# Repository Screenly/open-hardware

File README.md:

# open-hardware
Repository for Screenly's open hardware projects.

## License

Copyright Screenly, Inc.

This source describes Open Hardware and is licensed under the CERN-OHL-P v2 (SPDX: `CERN-OHL-P-2.0`). See [LICENSE](LICENSE) for the full text.

You may redistribute and modify this source and make products using it under the terms of the CERN-OHL-P v2 (https://cern.ch/cern-ohl).

This source is distributed WITHOUT ANY EXPRESS OR IMPLIED WARRANTY, INCLUDING OF MERCHANTABILITY, SATISFACTORY QUALITY AND FITNESS FOR A PARTICULAR PURPOSE. Please see the CERN-OHL-P v2 for applicable conditions.

Source location: https://github.com/Screenly/open-hardware

Third-party 3D models in `library/3d-models` come from component manufacturers and the KiCad libraries, and remain under their owners' terms.

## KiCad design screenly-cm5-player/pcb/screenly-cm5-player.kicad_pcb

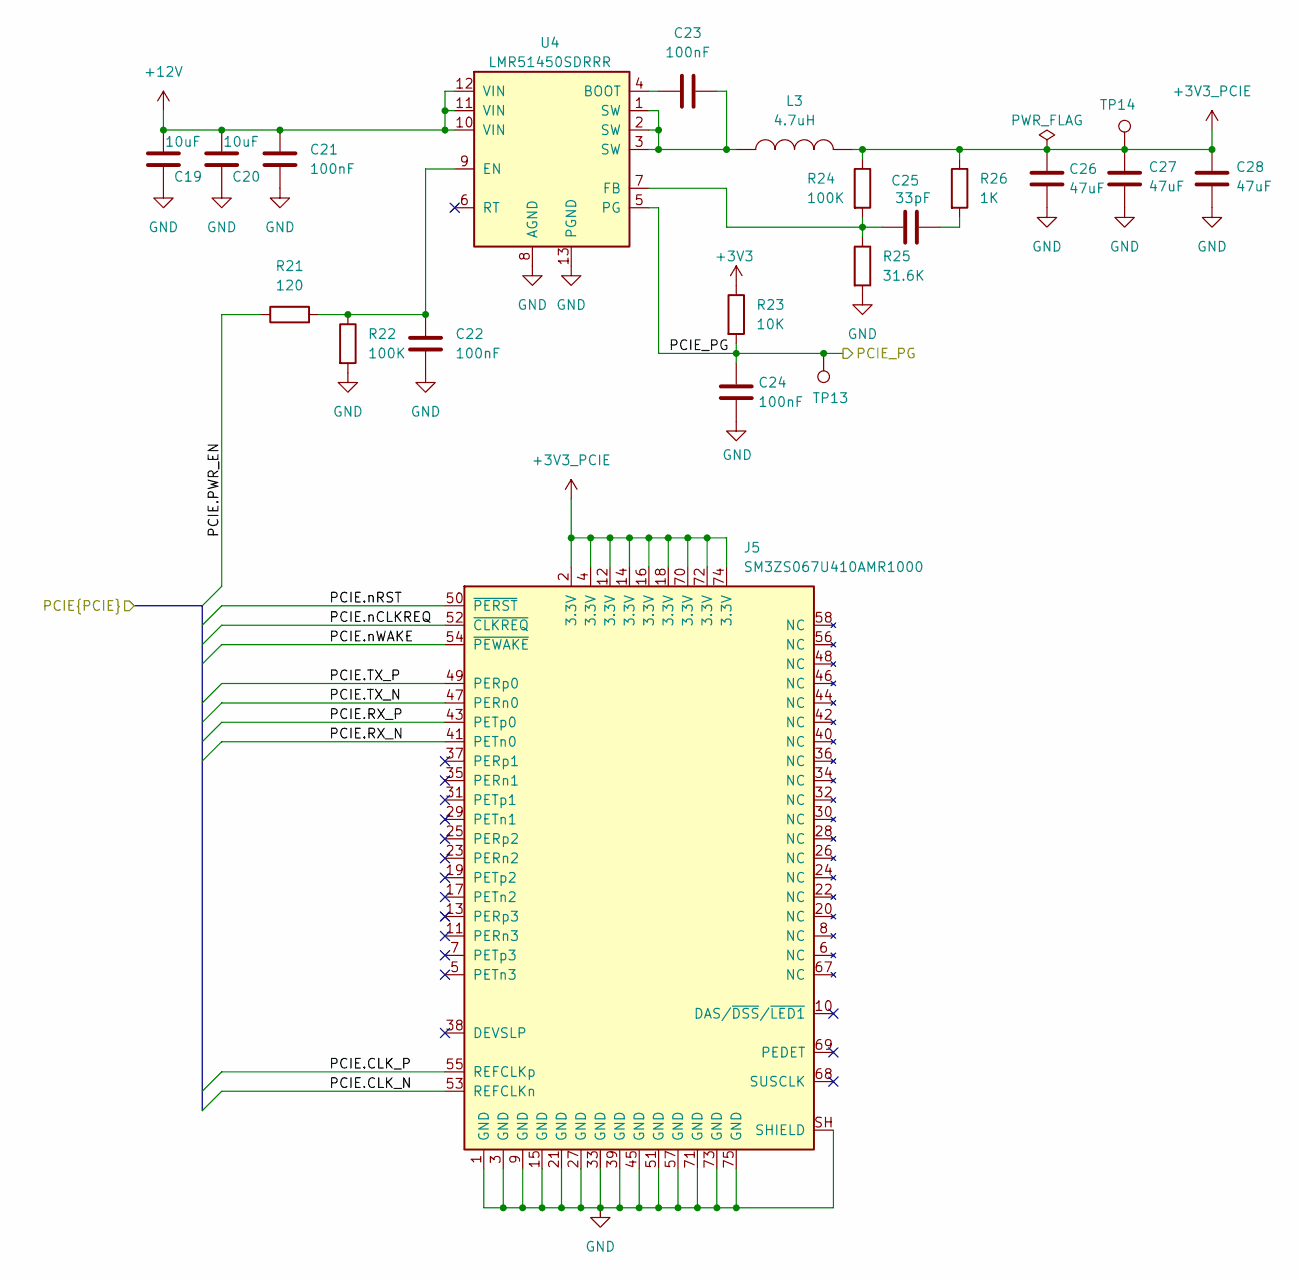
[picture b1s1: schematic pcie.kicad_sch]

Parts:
C19, C20: 10uF; C_1210; tolerance 10%; voltage 50V; PartNumber SRLY-CAP-000002
C21, C22, C23, C24: 100nF; C_0402; tolerance 10%; voltage 50V; PartNumber SRLY-CAP-000001
C25: 33pF; C_0402; tolerance 5%; voltage 50V; PartNumber SRLY-CAP-000003
C26, C27, C28: 47uF; C_1210; tolerance 10%; voltage 10V; PartNumber SRLY-CAP-000005
J5: SM3ZS067U410AMR1000; M2_M-Key_JAE_SM3ZS067U410AMR1000_2230_2242_2280; PartNumber SRLY-CON-000006
L3: 4.7uH; L_Coilank_AAPS1050; tolerance 20%; PartNumber SRLY-IND-000001
R21: 120; R_0402; tolerance 5%; voltage 50V; PartNumber SRLY-RES-000009
R22, R24: 100K; R_0402; tolerance 1%; voltage 50V; PartNumber SRLY-RES-000004
R23: 10K; R_0402; tolerance 1%; voltage 50V; PartNumber SRLY-RES-000005
R25: 31.6K; R_0402; tolerance 1%; voltage 50V; PartNumber SRLY-RES-000010
R26: 1K; R_0402; tolerance 5%; voltage 50V; PartNumber SRLY-RES-000006
TP13, TP14: TestPoint; TestPoint_Pad_D2.0mm
U4: LMR51450SDRRR; TI_WSON-12-1EP_3x3mm_P0.5mm_EP1.3x2.5mm; PartNumber SRLY-PWR-000001

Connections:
+3V3: R23.1; also elsewhere on the board
+3V3_PCIE: C26.1, C27.1, C28.1, J5.2 (3.3V), J5.4 (3.3V), J5.12 (3.3V), J5.14 (3.3V), J5.16 (3.3V), J5.18 (3.3V), J5.70 (3.3V), J5.72 (3.3V), J5.74 (3.3V), L3.2, R24.1, R26.1, TP14.1 (1_1)
+12V: C19.1, C20.1, C21.1, U4.10 (VIN), U4.11 (VIN), U4.12 (VIN); also elsewhere on the board
/Compute Module/PCIE.CLK_N: J5.53 (REFCLKn); also elsewhere on the board
/Compute Module/PCIE.CLK_P: J5.55 (REFCLKp); also elsewhere on the board
/Compute Module/PCIE.PWR_EN: R21.1; also elsewhere on the board
/Compute Module/PCIE.RX_N: J5.41 (PETn0); also elsewhere on the board
/Compute Module/PCIE.RX_P: J5.43 (PETp0); also elsewhere on the board
/Compute Module/PCIE.TX_N: J5.47 (PERn0); also elsewhere on the board
/Compute Module/PCIE.TX_P: J5.49 (PERp0); also elsewhere on the board
/Compute Module/PCIE.nCLKREQ: J5.52 (~CLKREQ); also elsewhere on the board
/Compute Module/PCIE.nRST: J5.50 (~PERST); also elsewhere on the board
/Compute Module/PCIE.nWAKE: J5.54 (~PEWAKE); also elsewhere on the board
/PCIE_PG: C24.2, R23.2, TP13.1 (1_1), U4.5 (PG); also elsewhere on the board
GND: C19.2, C20.2, C21.2, C22.1, C24.1, C26.2, C27.2, C28.2, J5.1 (GND), J5.3 (GND), J5.9 (GND), J5.15 (GND), J5.21 (GND), J5.27 (GND), J5.33 (GND), J5.39 (GND), J5.45 (GND), J5.51 (GND), J5.57 (GND), J5.71 (GND), J5.73 (GND), J5.75 (GND), J5.SH (SHIELD), R22.2, R25.2, U4.8 (AGND), U4.13 (PGND); also elsewhere on the board
unnamed: C23.2, L3.1, U4.1 (SW), U4.2 (SW), U4.3 (SW)
unnamed: C25.2, R26.2
unnamed: C23.1, U4.4 (BOOT)
unnamed: C22.2, R21.2, R22.1, U4.9 (EN)
unnamed: C25.1, R24.2, R25.1, U4.7 (FB)

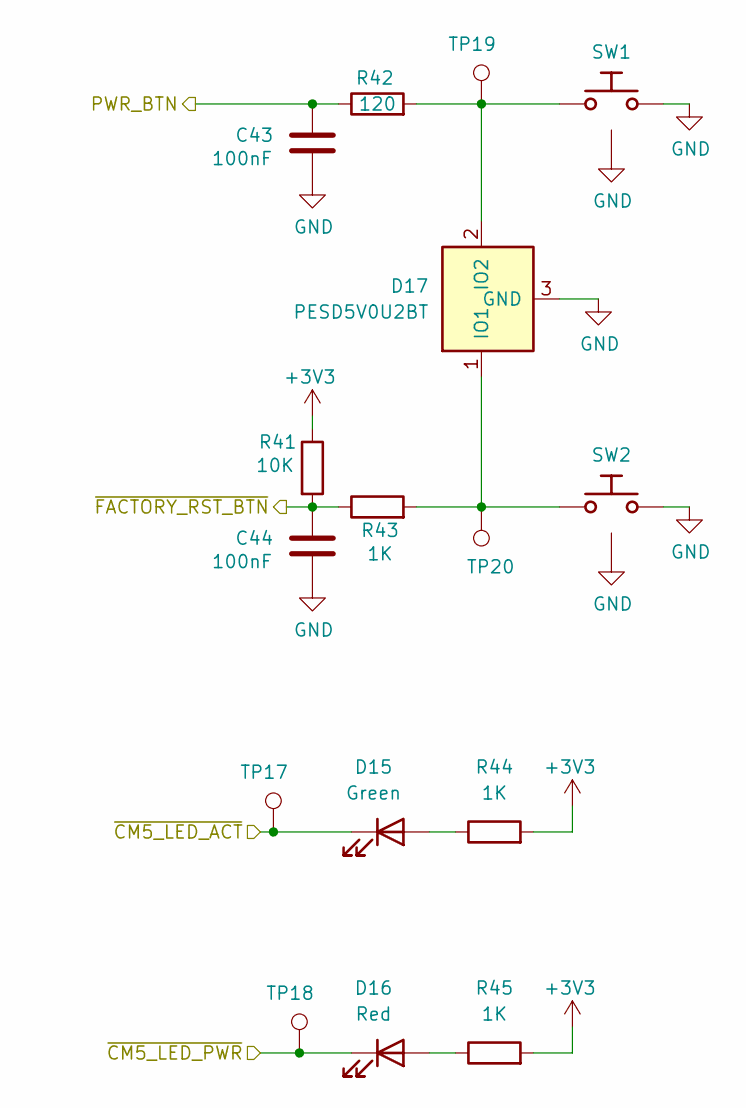
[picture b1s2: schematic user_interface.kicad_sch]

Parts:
C43, C44: 100nF; C_0402; tolerance 10%; voltage 50V; PartNumber SRLY-CAP-000001
D15: Green; LED_LiteOn_LTST-S270_SideView; PartNumber SRLY-LED-000002
D16: Red; LED_LiteOn_LTST-S270_SideView; PartNumber SRLY-LED-000001
D17: PESD5V0U2BT; SOT-23; PartNumber SRLY-DIO-000005
R41: 10K; R_0402; tolerance 1%; voltage 50V; PartNumber SRLY-RES-000005
R42: 120; R_0402; tolerance 5%; voltage 50V; PartNumber SRLY-RES-000009
R43, R44, R45: 1K; R_0402; tolerance 5%; voltage 50V; PartNumber SRLY-RES-000006
SW1, SW2: PTS645VM31-2; SW_Tactile_SPST_Angled_PTS645Vx58-2LFS; voltage 12V; PartNumber SRLY-SWC-000002
TP17, TP18, TP19, TP20: TestPoint; TestPoint_Pad_D2.0mm

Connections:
+3V3: R41.1, R44.2, R45.2; also elsewhere on the board
/Compute Module/PWR_BTN: C43.1, R42.1; also elsewhere on the board
/Compute Module/~CM5_LED_ACT: D15.1 (K), TP17.1 (1_1); also elsewhere on the board
/Compute Module/~CM5_LED_PWR: D16.1 (K), TP18.1 (1_1); also elsewhere on the board
/Compute Module/~FACTORY_RST_BTN: C44.1, R41.2, R43.1; also elsewhere on the board
GND: C43.2, C44.2, D17.3 (GND), SW1.2, SW1.SH, SW2.2, SW2.SH; also elsewhere on the board
unnamed: D15.2 (A), R44.1
unnamed: D16.2 (A), R45.1
unnamed: D17.1 (IO1), R43.2, SW2.1, TP20.1 (1_1)
unnamed: D17.2 (IO2), R42.2, SW1.1, TP19.1 (1_1)

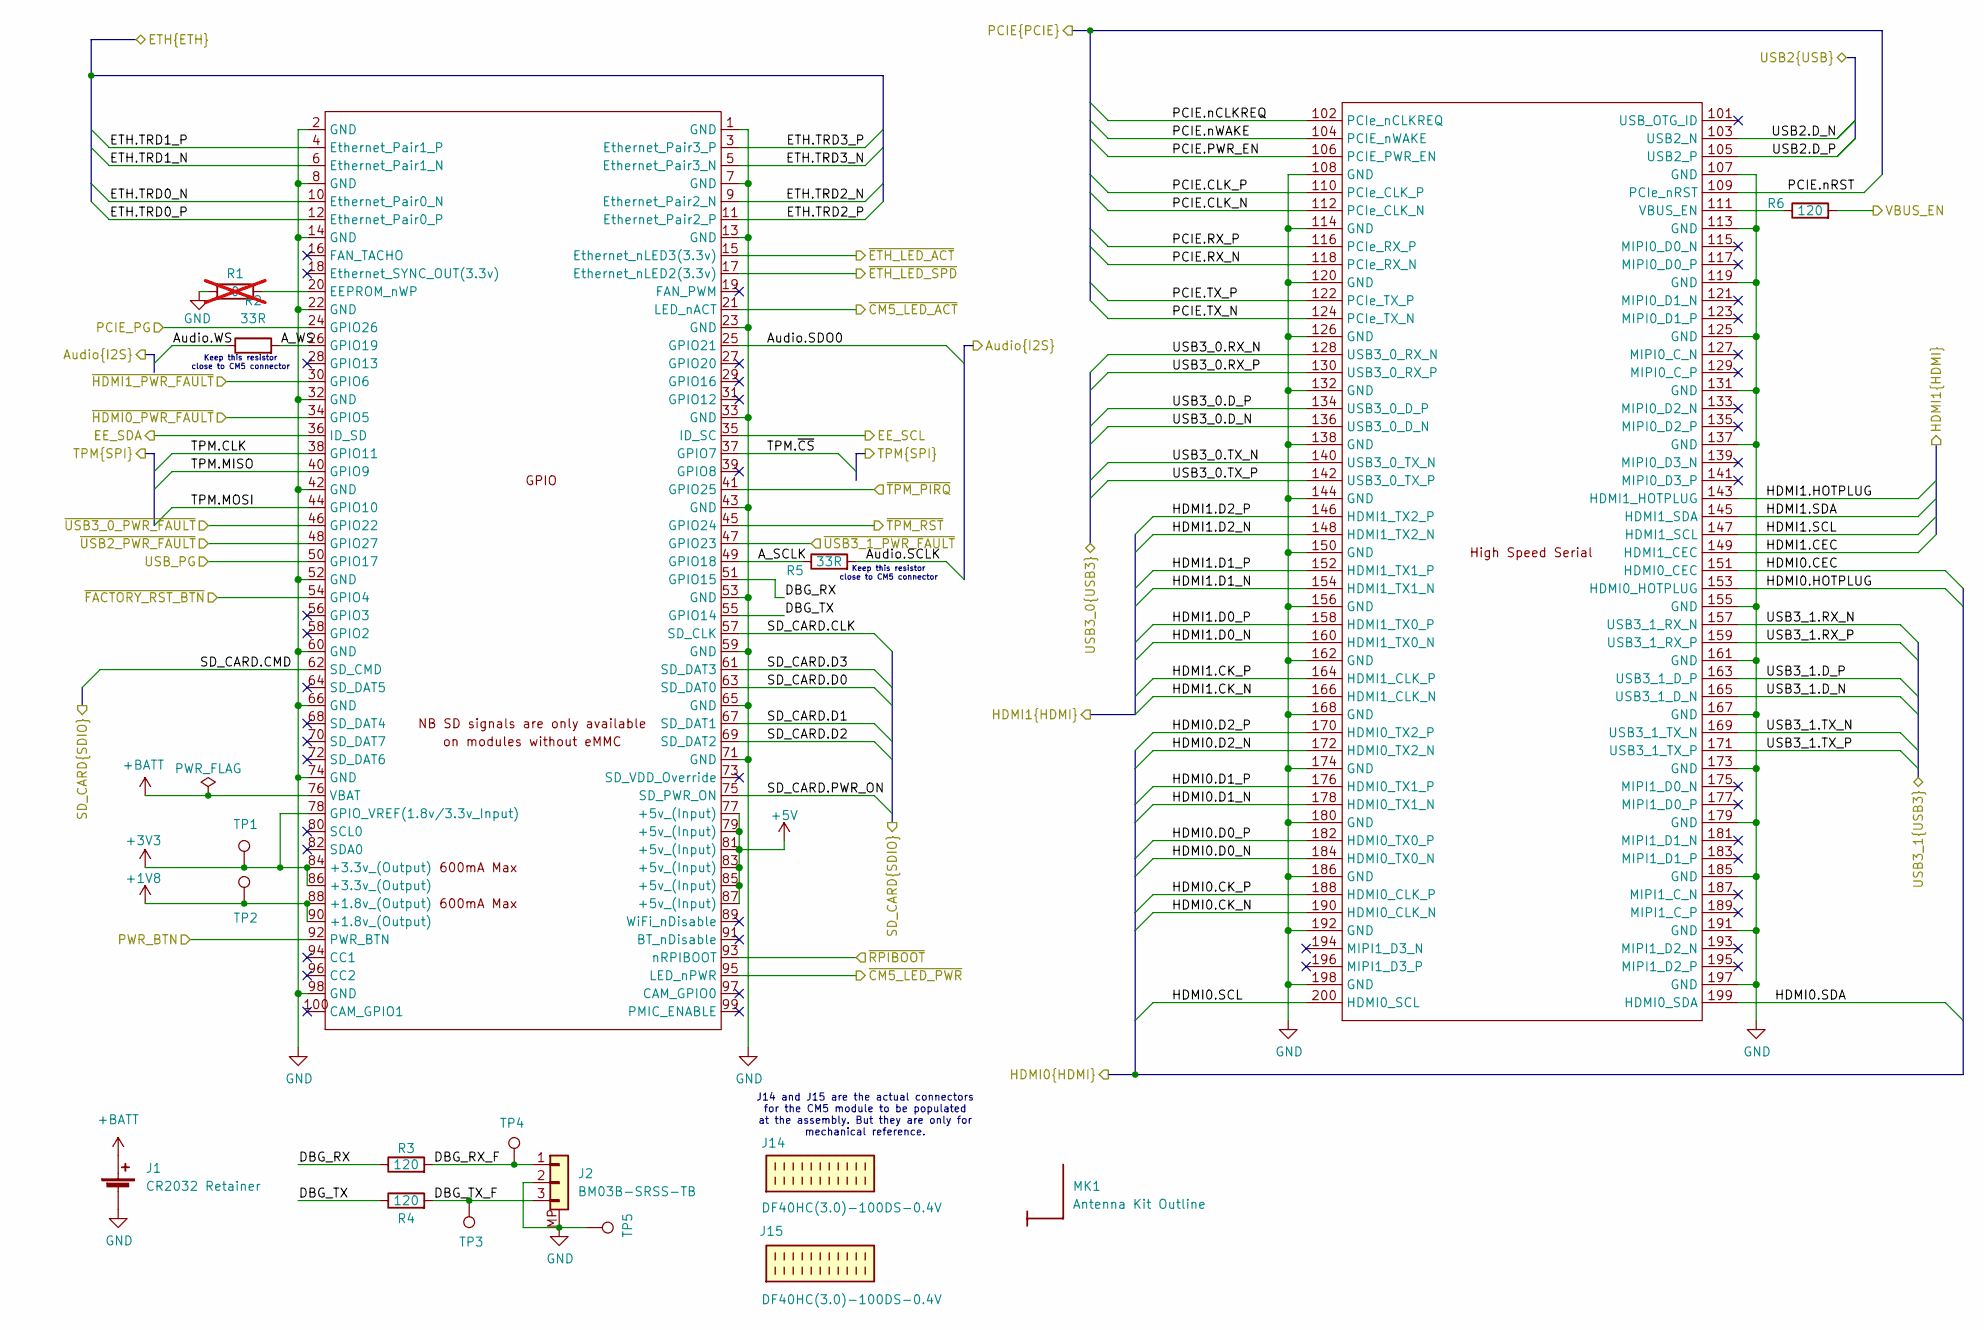
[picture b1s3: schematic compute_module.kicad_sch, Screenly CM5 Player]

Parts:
J1: CR2032 Retainer; BatteryHolder_MYOUNG_MY-2032-08_CR2032; PartNumber SRLY-CON-000014
J2: BM03B-SRSS-TB; JST_SH_BM03B-SRSS-TB_1x03-1MP_P1.00mm_Vertical; voltage 50V; PartNumber SRLY-CON-000015
J14, J15: DF40HC(3.0)-100DS-0.4V; Hirose_DF40HC-3.0-100DS-0.4V_2x50_P0.4mm_Vertical_NoCopper; PartNumber SRLY-CON-000016
MK1: Antenna Kit Outline; RaspberryPi_Antenna_Kit_Outline_SideView
R1: 0; SolderBridge_0402; tolerance 1%; voltage 50V; PartNumber SRLY-RES-000008; not fitted
R2, R5: 33R; R_0402; tolerance 5%; voltage 50V; PartNumber SRLY-RES-000014
R3, R4, R6: 120; R_0402; tolerance 5%; voltage 50V; PartNumber SRLY-RES-000009
TP1, TP2, TP3, TP4, TP5: TestPoint; TestPoint_Pad_D2.0mm
U1: CM5104064; RaspberryPi-CM5; PartNumber SRLY-MOD-000001

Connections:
+1V8: TP2.1 (1_1), U1.88 (+1.8v_(Output)), U1.90 (+1.8v_(Output))
+3V3: TP1.1 (1_1), U1.78 (GPIO_VREF(1.8v/3.3v_Input)), U1.84 (+3.3v_(Output)), U1.86 (+3.3v_(Output)); also elsewhere on the board
+5V: U1.77 (+5v_(Input)), U1.79 (+5v_(Input)), U1.81 (+5v_(Input)), U1.83 (+5v_(Input)), U1.85 (+5v_(Input)), U1.87 (+5v_(Input)); also elsewhere on the board
+BATT: J1.1 (+), U1.76 (VBAT)
/Analog Audio/Audio.SCLK: R5.2; also elsewhere on the board
/Analog Audio/Audio.SDO0: U1.25 (GPIO21); also elsewhere on the board
/Analog Audio/Audio.WS: R2.1; also elsewhere on the board
/Compute Module/A_SCLK: R5.1, U1.49 (GPIO18)
/Compute Module/A_WS: R2.2, U1.26 (GPIO19)
/Compute Module/DBG_RX: R3.1, U1.51 (GPIO15)
/Compute Module/DBG_RX_F: J2.1, R3.2, TP4.1 (1_1)
/Compute Module/DBG_TX: R4.1, U1.55 (GPIO14)
/Compute Module/DBG_TX_F: J2.3, R4.2, TP3.1 (1_1)
/Compute Module/EE_SCL: U1.35 (ID_SC); also elsewhere on the board
/Compute Module/EE_SDA: U1.36 (ID_SD); also elsewhere on the board
/Compute Module/ETH.TRD0_N: U1.10 (Ethernet_Pair0_N); also elsewhere on the board
/Compute Module/ETH.TRD0_P: U1.12 (Ethernet_Pair0_P); also elsewhere on the board
/Compute Module/ETH.TRD1_N: U1.6 (Ethernet_Pair1_N); also elsewhere on the board
/Compute Module/ETH.TRD1_P: U1.4 (Ethernet_Pair1_P); also elsewhere on the board
/Compute Module/ETH.TRD2_N: U1.9 (Ethernet_Pair2_N); also elsewhere on the board
/Compute Module/ETH.TRD2_P: U1.11 (Ethernet_Pair2_P); also elsewhere on the board
/Compute Module/ETH.TRD3_N: U1.5 (Ethernet_Pair3_N); also elsewhere on the board
/Compute Module/ETH.TRD3_P: U1.3 (Ethernet_Pair3_P); also elsewhere on the board
/Compute Module/HDMI0.CEC: U1.151 (HDMI0_CEC); also elsewhere on the board
/Compute Module/HDMI0.CK_N: U1.190 (HDMI0_CLK_N); also elsewhere on the board
/Compute Module/HDMI0.CK_P: U1.188 (HDMI0_CLK_P); also elsewhere on the board
/Compute Module/HDMI0.D0_N: U1.184 (HDMI0_TX0_N); also elsewhere on the board
/Compute Module/HDMI0.D0_P: U1.182 (HDMI0_TX0_P); also elsewhere on the board
/Compute Module/HDMI0.D1_N: U1.178 (HDMI0_TX1_N); also elsewhere on the board
/Compute Module/HDMI0.D1_P: U1.176 (HDMI0_TX1_P); also elsewhere on the board
/Compute Module/HDMI0.D2_N: U1.172 (HDMI0_TX2_N); also elsewhere on the board
/Compute Module/HDMI0.D2_P: U1.170 (HDMI0_TX2_P); also elsewhere on the board
/Compute Module/HDMI0.HOTPLUG: U1.153 (HDMI0_HOTPLUG); also elsewhere on the board
/Compute Module/HDMI0.SCL: U1.200 (HDMI0_SCL); also elsewhere on the board
/Compute Module/HDMI0.SDA: U1.199 (HDMI0_SDA); also elsewhere on the board
/Compute Module/HDMI1.CEC: U1.149 (HDMI1_CEC); also elsewhere on the board
/Compute Module/HDMI1.CK_N: U1.166 (HDMI1_CLK_N); also elsewhere on the board
/Compute Module/HDMI1.CK_P: U1.164 (HDMI1_CLK_P); also elsewhere on the board
/Compute Module/HDMI1.D0_N: U1.160 (HDMI1_TX0_N); also elsewhere on the board
/Compute Module/HDMI1.D0_P: U1.158 (HDMI1_TX0_P); also elsewhere on the board
/Compute Module/HDMI1.D1_N: U1.154 (HDMI1_TX1_N); also elsewhere on the board
/Compute Module/HDMI1.D1_P: U1.152 (HDMI1_TX1_P); also elsewhere on the board
/Compute Module/HDMI1.D2_N: U1.148 (HDMI1_TX2_N); also elsewhere on the board
/Compute Module/HDMI1.D2_P: U1.146 (HDMI1_TX2_P); also elsewhere on the board
/Compute Module/HDMI1.HOTPLUG: U1.143 (HDMI1_HOTPLUG); also elsewhere on the board
/Compute Module/HDMI1.SCL: U1.147 (HDMI1_SCL); also elsewhere on the board
/Compute Module/HDMI1.SDA: U1.145 (HDMI1_SDA); also elsewhere on the board
/Compute Module/PCIE.CLK_N: U1.112 (PCIe_CLK_N); also elsewhere on the board
/Compute Module/PCIE.CLK_P: U1.110 (PCIe_CLK_P); also elsewhere on the board
/Compute Module/PCIE.PWR_EN: U1.106 (PCIE_PWR_EN); also elsewhere on the board
/Compute Module/PCIE.RX_N: U1.118 (PCIe_RX_N); also elsewhere on the board
/Compute Module/PCIE.RX_P: U1.116 (PCIe_RX_P); also elsewhere on the board
/Compute Module/PCIE.TX_N: U1.124 (PCIe_TX_N); also elsewhere on the board
/Compute Module/PCIE.TX_P: U1.122 (PCIe_TX_P); also elsewhere on the board
/Compute Module/PCIE.nCLKREQ: U1.102 (PCIe_nCLKREQ); also elsewhere on the board
/Compute Module/PCIE.nRST: U1.109 (PCIe_nRST); also elsewhere on the board
/Compute Module/PCIE.nWAKE: U1.104 (PCIE_nWAKE); also elsewhere on the board
/Compute Module/PWR_BTN: U1.92 (PWR_BTN); also elsewhere on the board
/Compute Module/SD_CARD.CLK: U1.57 (SD_CLK); also elsewhere on the board
/Compute Module/SD_CARD.CMD: U1.62 (SD_CMD); also elsewhere on the board
/Compute Module/SD_CARD.D0: U1.63 (SD_DAT0); also elsewhere on the board
/Compute Module/SD_CARD.D1: U1.67 (SD_DAT1); also elsewhere on the board
/Compute Module/SD_CARD.D2: U1.69 (SD_DAT2); also elsewhere on the board
/Compute Module/SD_CARD.D3: U1.61 (SD_DAT3); also elsewhere on the board
/Compute Module/SD_CARD.PWR_ON: U1.75 (SD_PWR_ON); also elsewhere on the board
/Compute Module/TPM.CLK: U1.38 (GPIO11); also elsewhere on the board
/Compute Module/TPM.MISO: U1.40 (GPIO9); also elsewhere on the board
/Compute Module/TPM.MOSI: U1.44 (GPIO10); also elsewhere on the board
/Compute Module/TPM.~CS: U1.37 (GPIO7); also elsewhere on the board
/Compute Module/USB2.D_N: U1.103 (USB2_N); also elsewhere on the board
/Compute Module/USB2.D_P: U1.105 (USB2_P); also elsewhere on the board
/Compute Module/USB3_0.D_N: U1.136 (USB3_0_D_N); also elsewhere on the board
/Compute Module/USB3_0.D_P: U1.134 (USB3_0_D_P); also elsewhere on the board
/Compute Module/USB3_0.RX_N: U1.128 (USB3_0_RX_N); also elsewhere on the board
/Compute Module/USB3_0.RX_P: U1.130 (USB3_0_RX_P); also elsewhere on the board
/Compute Module/USB3_0.TX_N: U1.140 (USB3_0_TX_N); also elsewhere on the board
/Compute Module/USB3_0.TX_P: U1.142 (USB3_0_TX_P); also elsewhere on the board
/Compute Module/USB3_1.D_N: U1.165 (USB3_1_D_N); also elsewhere on the board
/Compute Module/USB3_1.D_P: U1.163 (USB3_1_D_P); also elsewhere on the board
/Compute Module/USB3_1.RX_N: U1.157 (USB3_1_RX_N); also elsewhere on the board
/Compute Module/USB3_1.RX_P: U1.159 (USB3_1_RX_P); also elsewhere on the board
/Compute Module/USB3_1.TX_N: U1.169 (USB3_1_TX_N); also elsewhere on the board
/Compute Module/USB3_1.TX_P: U1.171 (USB3_1_TX_P); also elsewhere on the board
/Compute Module/VBUS_EN: R6.2; also elsewhere on the board
/Compute Module/~CM5_LED_ACT: U1.21 (LED_nACT); also elsewhere on the board
/Compute Module/~CM5_LED_PWR: U1.95 (LED_nPWR); also elsewhere on the board
/Compute Module/~ETH_LED_ACT: U1.15 (Ethernet_nLED3(3.3v)); also elsewhere on the board
/Compute Module/~ETH_LED_SPD: U1.17 (Ethernet_nLED2(3.3v)); also elsewhere on the board
/Compute Module/~FACTORY_RST_BTN: U1.54 (GPIO4); also elsewhere on the board
/Compute Module/~HDMI0_PWR_FAULT: U1.34 (GPIO5); also elsewhere on the board
/Compute Module/~HDMI1_PWR_FAULT: U1.30 (GPIO6); also elsewhere on the board
/Compute Module/~RPIBOOT: U1.93 (nRPIBOOT); also elsewhere on the board
/Compute Module/~TPM_PIRQ: U1.41 (GPIO25); also elsewhere on the board
/Compute Module/~TPM_RST: U1.45 (GPIO24); also elsewhere on the board
/Compute Module/~USB2_PWR_FAULT: U1.48 (GPIO27); also elsewhere on the board
/Compute Module/~USB3_0_PWR_FAULT: U1.46 (GPIO22); also elsewhere on the board
/Compute Module/~USB3_1_PWR_FAULT: U1.47 (GPIO23); also elsewhere on the board
/PCIE_PG: U1.24 (GPIO26); also elsewhere on the board
/USB_PG: U1.50 (GPIO17); also elsewhere on the board
GND: J1.2 (-), J2.2, J2.MP, R1.1, TP5.1 (1_1), U1.1 (GND), U1.2 (GND), U1.7 (GND), U1.8 (GND), U1.13 (GND), U1.14 (GND), U1.22 (GND), U1.23 (GND), U1.32 (GND), U1.33 (GND), U1.42 (GND), U1.43 (GND), U1.52 (GND), U1.53 (GND), U1.59 (GND), U1.60 (GND), U1.65 (GND), U1.66 (GND), U1.71 (GND), U1.74 (GND), U1.98 (GND), U1.107 (GND), U1.108 (GND), U1.113 (GND), U1.114 (GND), U1.119 (GND), U1.120 (GND), U1.125 (GND), U1.126 (GND), U1.131 (GND), U1.132 (GND), U1.137 (GND), U1.138 (GND), U1.144 (GND), U1.150 (GND), U1.155 (GND), U1.156 (GND), U1.161 (GND), U1.162 (GND), U1.167 (GND), U1.168 (GND), U1.173 (GND), U1.174 (GND), U1.179 (GND), U1.180 (GND), U1.185 (GND), U1.186 (GND), U1.191 (GND), U1.192 (GND), U1.197 (GND), U1.198 (GND); also elsewhere on the board
unnamed: R1.2, U1.20 (EEPROM_nWP)
unnamed: R6.1, U1.111 (VBUS_EN)

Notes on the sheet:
Keep this resistor close to CM5 connector
J14 and J15 are the actual connectors for the CM5 module to be populated at the assembly. But they are only for mechanical reference.

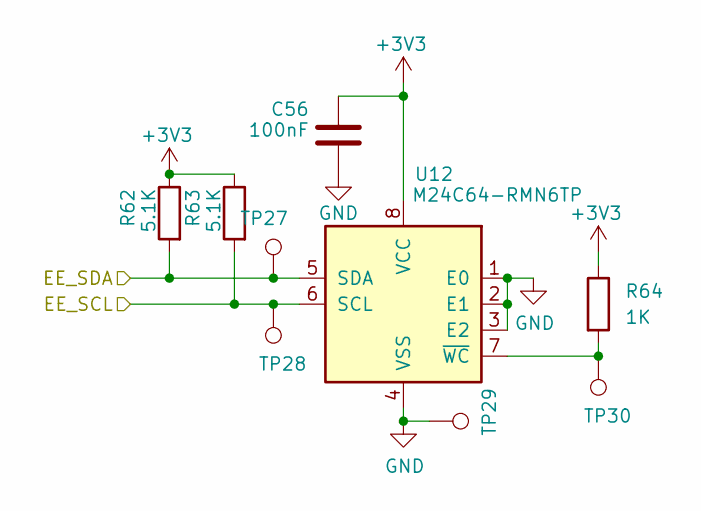
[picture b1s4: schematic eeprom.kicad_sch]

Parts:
C56: 100nF; C_0402; tolerance 10%; voltage 50V; PartNumber SRLY-CAP-000001
R62, R63: 5.1K; R_0402; tolerance 1%; voltage 50V; PartNumber SRLY-RES-000012
R64: 1K; R_0402; tolerance 5%; voltage 50V; PartNumber SRLY-RES-000006
TP27, TP28, TP29, TP30: TestPoint; TestPoint_Pad_D2.0mm
U12: M24C64-RMN6TP; SOIC-8_3.9x4.9mm_P1.27mm; PartNumber SRLY-STO-000001

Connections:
+3V3: C56.1, R62.1, R63.1, R64.1, U12.8 (VCC); also elsewhere on the board
/Compute Module/EE_SCL: R63.2, TP28.1 (1_1), U12.6 (SCL); also elsewhere on the board
/Compute Module/EE_SDA: R62.2, TP27.1 (1_1), U12.5 (SDA); also elsewhere on the board
GND: C56.2, TP29.1 (1_1), U12.1 (E0), U12.2 (E1), U12.3 (E2), U12.4 (VSS); also elsewhere on the board
unnamed: R64.2, TP30.1 (1_1), U12.7 (~WC)

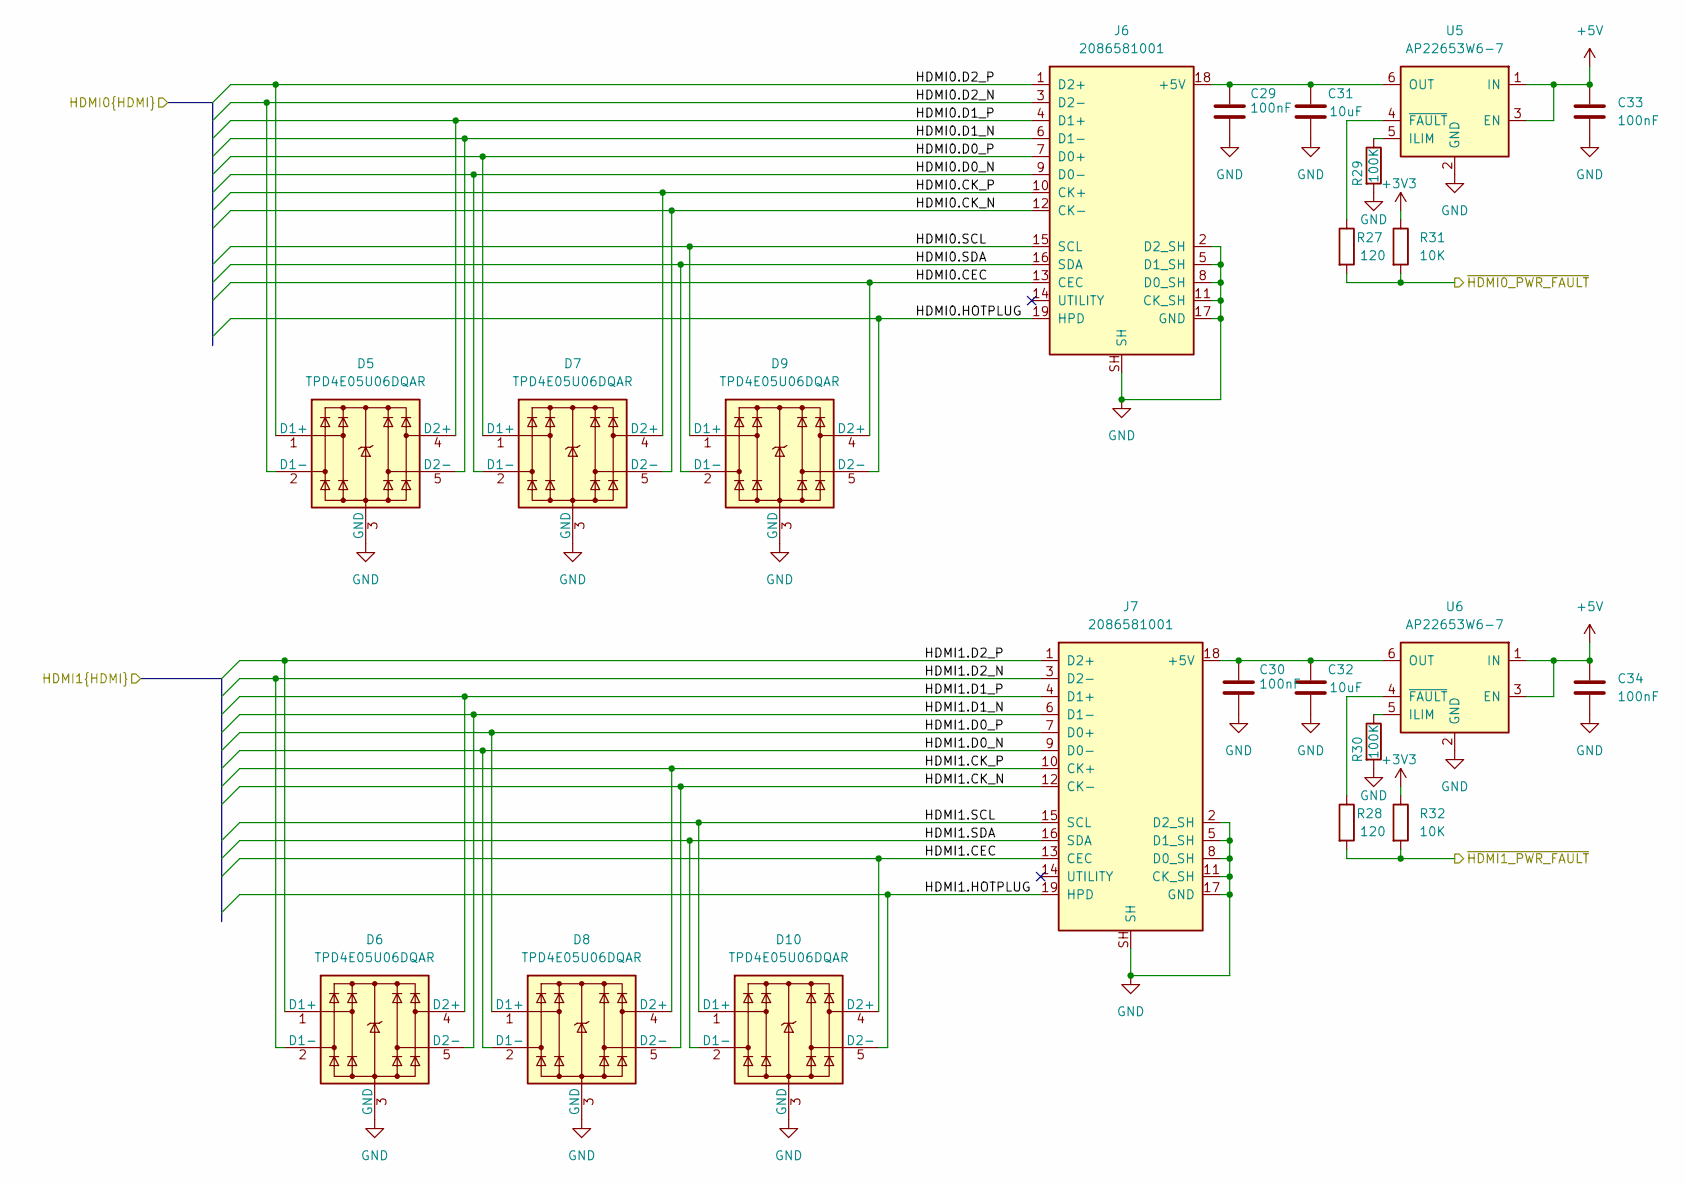
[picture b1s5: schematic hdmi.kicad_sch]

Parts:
C29, C30, C33, C34: 100nF; C_0402; tolerance 10%; voltage 50V; PartNumber SRLY-CAP-000001
C31, C32: 10uF; C_1210; tolerance 10%; voltage 50V; PartNumber SRLY-CAP-000002
D5, D6, D7, D8, D9, D10: TPD4E05U06DQAR; TI_USON-10_2.5x1.0mm_P0.5mm; PartNumber SRLY-DIO-000004
J6, J7: 2086581001; HDMI_A_Molex_208658-1001_Horizontal; voltage 40V; PartNumber SRLY-CON-000007
R27, R28: 120; R_0402; tolerance 5%; voltage 50V; PartNumber SRLY-RES-000009
R29, R30: 100K; R_0402; tolerance 1%; voltage 50V; PartNumber SRLY-RES-000004
R31, R32: 10K; R_0402; tolerance 1%; voltage 50V; PartNumber SRLY-RES-000005
U5, U6: AP22653W6-7; SOT-23-6; PartNumber SRLY-PWR-000003

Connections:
+3V3: R31.1, R32.1; also elsewhere on the board
+5V: C33.1, C34.1, U5.1 (IN), U5.3 (EN), U6.1 (IN), U6.3 (EN); also elsewhere on the board
/Compute Module/HDMI0.CEC: D9.4 (D2+), D9.7, J6.13 (CEC); also elsewhere on the board
/Compute Module/HDMI0.CK_N: D7.5 (D2-), D7.6, J6.12 (CK-); also elsewhere on the board
/Compute Module/HDMI0.CK_P: D7.4 (D2+), D7.7, J6.10 (CK+); also elsewhere on the board
/Compute Module/HDMI0.D0_N: D7.2 (D1-), D7.9, J6.9 (D0-); also elsewhere on the board
/Compute Module/HDMI0.D0_P: D7.1 (D1+), D7.10, J6.7 (D0+); also elsewhere on the board
/Compute Module/HDMI0.D1_N: D5.5 (D2-), D5.6, J6.6 (D1-); also elsewhere on the board
/Compute Module/HDMI0.D1_P: D5.4 (D2+), D5.7, J6.4 (D1+); also elsewhere on the board
/Compute Module/HDMI0.D2_N: D5.2 (D1-), D5.9, J6.3 (D2-); also elsewhere on the board
/Compute Module/HDMI0.D2_P: D5.1 (D1+), D5.10, J6.1 (D2+); also elsewhere on the board
/Compute Module/HDMI0.HOTPLUG: D9.5 (D2-), D9.6, J6.19 (HPD); also elsewhere on the board
/Compute Module/HDMI0.SCL: D9.1 (D1+), D9.10, J6.15 (SCL); also elsewhere on the board
/Compute Module/HDMI0.SDA: D9.2 (D1-), D9.9, J6.16 (SDA); also elsewhere on the board
/Compute Module/HDMI1.CEC: D10.4 (D2+), D10.7, J7.13 (CEC); also elsewhere on the board
/Compute Module/HDMI1.CK_N: D8.5 (D2-), D8.6, J7.12 (CK-); also elsewhere on the board
/Compute Module/HDMI1.CK_P: D8.4 (D2+), D8.7, J7.10 (CK+); also elsewhere on the board
/Compute Module/HDMI1.D0_N: D8.2 (D1-), D8.9, J7.9 (D0-); also elsewhere on the board
/Compute Module/HDMI1.D0_P: D8.1 (D1+), D8.10, J7.7 (D0+); also elsewhere on the board
/Compute Module/HDMI1.D1_N: D6.5 (D2-), D6.6, J7.6 (D1-); also elsewhere on the board
/Compute Module/HDMI1.D1_P: D6.4 (D2+), D6.7, J7.4 (D1+); also elsewhere on the board
/Compute Module/HDMI1.D2_N: D6.2 (D1-), D6.9, J7.3 (D2-); also elsewhere on the board
/Compute Module/HDMI1.D2_P: D6.1 (D1+), D6.10, J7.1 (D2+); also elsewhere on the board
/Compute Module/HDMI1.HOTPLUG: D10.5 (D2-), D10.6, J7.19 (HPD); also elsewhere on the board
/Compute Module/HDMI1.SCL: D10.1 (D1+), D10.10, J7.15 (SCL); also elsewhere on the board
/Compute Module/HDMI1.SDA: D10.2 (D1-), D10.9, J7.16 (SDA); also elsewhere on the board
/Compute Module/~HDMI0_PWR_FAULT: R27.2, R31.2; also elsewhere on the board
/Compute Module/~HDMI1_PWR_FAULT: R28.2, R32.2; also elsewhere on the board
GND: C29.2, C30.2, C31.2, C32.2, C33.2, C34.2, D5.3 (GND), D5.8 (GND), D6.3 (GND), D6.8 (GND), D7.3 (GND), D7.8 (GND), D8.3 (GND), D8.8 (GND), D9.3 (GND), D9.8 (GND), D10.3 (GND), D10.8 (GND), J6.2 (D2_SH), J6.5 (D1_SH), J6.8 (D0_SH), J6.11 (CK_SH), J6.17 (GND), J6.SH, J7.2 (D2_SH), J7.5 (D1_SH), J7.8 (D0_SH), J7.11 (CK_SH), J7.17 (GND), J7.SH, R29.2, R30.2, U5.2 (GND), U6.2 (GND); also elsewhere on the board
unnamed: C29.1, C31.1, J6.18 (+5V), U5.6 (OUT)
unnamed: C30.1, C32.1, J7.18 (+5V), U6.6 (OUT)
unnamed: R29.1, U5.5 (ILIM)
unnamed: R27.1, U5.4 (~FAULT)
unnamed: R30.1, U6.5 (ILIM)
unnamed: R28.1, U6.4 (~FAULT)

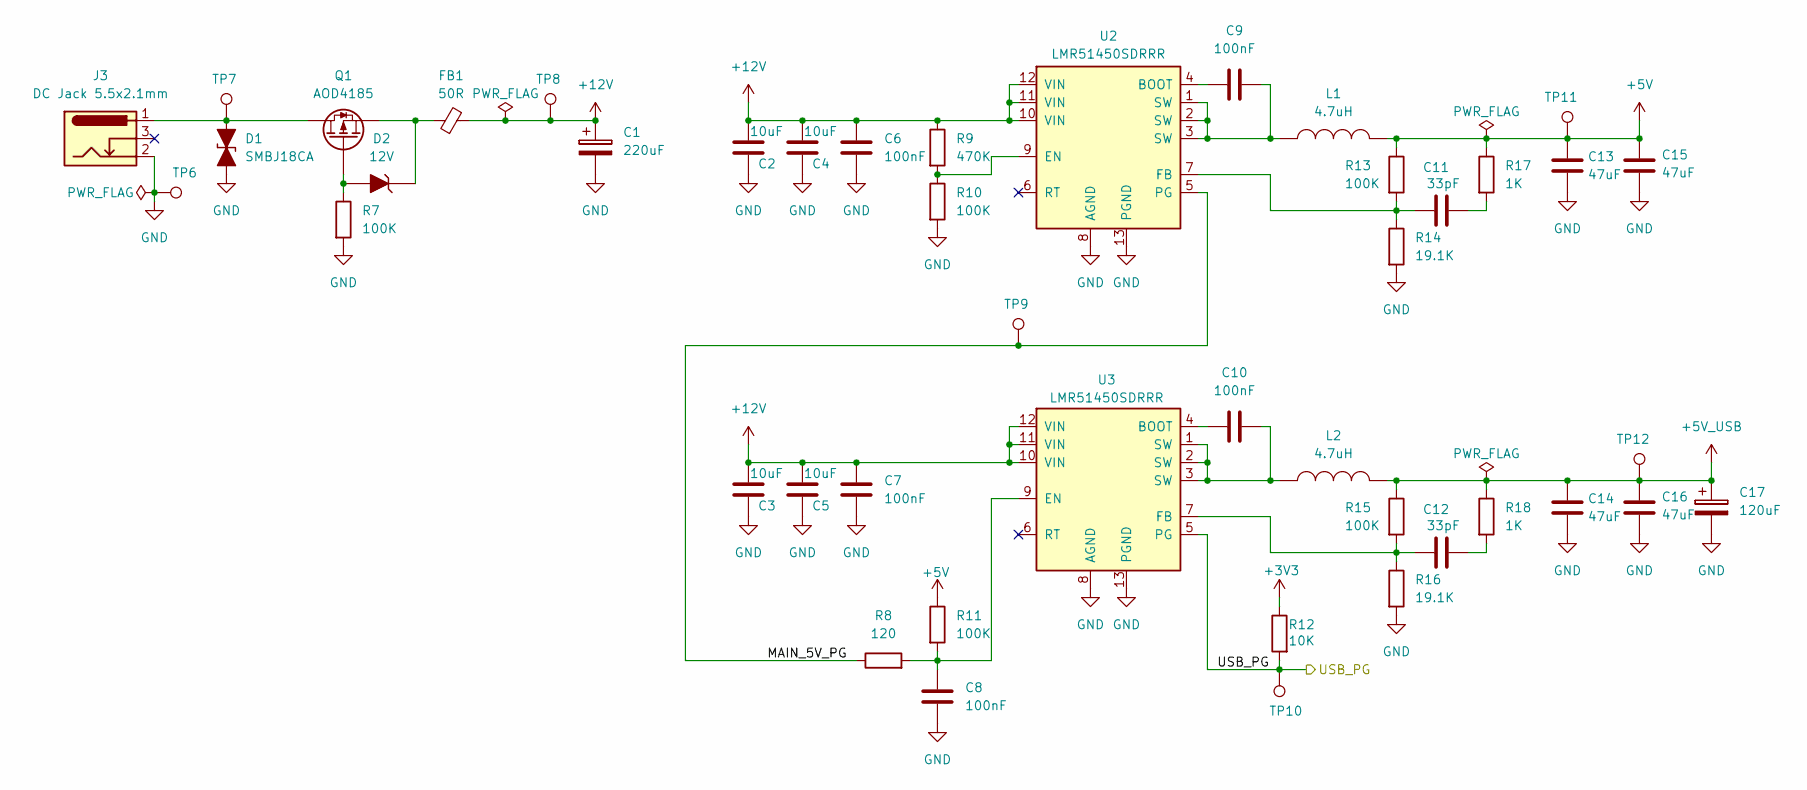
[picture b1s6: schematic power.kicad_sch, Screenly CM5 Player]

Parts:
C1: 220uF; CP_Radial_D6.3mm_P2.50mm; tolerance 20%; voltage 35V; PartNumber SRLY-CAP-000008
C2, C3, C4, C5: 10uF; C_1210; tolerance 10%; voltage 50V; PartNumber SRLY-CAP-000002
C6, C7, C8, C9, C10: 100nF; C_0402; tolerance 10%; voltage 50V; PartNumber SRLY-CAP-000001
C11, C12: 33pF; C_0402; tolerance 5%; voltage 50V; PartNumber SRLY-CAP-000003
C13, C14, C15, C16: 47uF; C_1210; tolerance 10%; voltage 10V; PartNumber SRLY-CAP-000005
C17: 120uF; CP_Elec_6.3x5.9; tolerance 20%; voltage 10V; PartNumber SRLY-CAP-000006
D1: SMBJ18CA; D_SMB; PartNumber SRLY-DIO-000001
D2: 12V; D_SOD-123; tolerance 6%; PartNumber SRLY-DIO-000002
FB1: 50R; FB_1206; PartNumber SRLY-FBD-000001
J3: DC Jack 5.5x2.1mm; BarrelJack_Tensility_54-00129_Horizontal; voltage 57V; PartNumber SRLY-CON-000004
L1, L2: 4.7uH; L_Coilank_AAPS1050; tolerance 20%; PartNumber SRLY-IND-000001
Q1: AOD4185; TO-252-2; PartNumber SRLY-FET-000001
R7, R10, R11, R13, R15: 100K; R_0402; tolerance 1%; voltage 50V; PartNumber SRLY-RES-000004
R8: 120; R_0402; tolerance 5%; voltage 50V; PartNumber SRLY-RES-000009
R9: 470K; R_0402; tolerance 5%; voltage 50V; PartNumber SRLY-RES-000003
R12: 10K; R_0402; tolerance 1%; voltage 50V; PartNumber SRLY-RES-000005
R14, R16: 19.1K; R_0402; tolerance 1%; voltage 50V; PartNumber SRLY-RES-000007
R17, R18: 1K; R_0402; tolerance 5%; voltage 50V; PartNumber SRLY-RES-000006
TP6, TP7, TP8, TP9, TP10, TP11, TP12: TestPoint; TestPoint_Pad_D2.0mm
U2, U3: LMR51450SDRRR; TI_WSON-12-1EP_3x3mm_P0.5mm_EP1.3x2.5mm; PartNumber SRLY-PWR-000001

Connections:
+3V3: R12.1; also elsewhere on the board
+5V: C13.1, C15.1, L1.2, R11.1, R13.1, R17.1, TP11.1 (1_1); also elsewhere on the board
+5V_USB: C14.1, C16.1, C17.1, L2.2, R15.1, R18.1, TP12.1 (1_1); also elsewhere on the board
+12V: C1.1, C2.1, C3.1, C4.1, C5.1, C6.1, C7.1, FB1.2, R9.1, TP8.1 (1_1), U2.10 (VIN), U2.11 (VIN), U2.12 (VIN), U3.10 (VIN), U3.11 (VIN), U3.12 (VIN); also elsewhere on the board
/Power/MAIN_5V_PG: R8.1, TP9.1 (1_1), U2.5 (PG)
/USB_PG: R12.2, TP10.1 (1_1), U3.5 (PG); also elsewhere on the board
GND: C1.2, C2.2, C3.2, C4.2, C5.2, C6.2, C7.2, C8.1, C13.2, C14.2, C15.2, C16.2, C17.2, D1.2 (A2), J3.2, R7.2, R10.2, R14.2, R16.2, TP6.1 (1_1), U2.8 (AGND), U2.13 (PGND), U3.8 (AGND), U3.13 (PGND); also elsewhere on the board
unnamed: C9.2, L1.1, U2.1 (SW), U2.2 (SW), U2.3 (SW)
unnamed: C10.2, L2.1, U3.1 (SW), U3.2 (SW), U3.3 (SW)
unnamed: C11.2, R17.2
unnamed: C12.2, R18.2
unnamed: D1.1 (A1), J3.1, Q1.2 (D), TP7.1 (1_1)
unnamed: D2.2 (A), Q1.1 (G), R7.1
unnamed: D2.1 (K), FB1.1, Q1.3 (S)
unnamed: C9.1, U2.4 (BOOT)
unnamed: R9.2, R10.1, U2.9 (EN)
unnamed: C11.1, R13.2, R14.1, U2.7 (FB)
unnamed: C10.1, U3.4 (BOOT)
unnamed: C8.2, R8.2, R11.2, U3.9 (EN)
unnamed: C12.1, R15.2, R16.1, U3.7 (FB)
